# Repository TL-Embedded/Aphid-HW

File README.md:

# Aphid-HW

The Aphid Debugger provides a SWD and UART link via FT2232.

The 10 pin connector is compatible with the [10 pin standard here](https://github.com/TL-Embedded/SWD-UART-CTX-10).

The DTR signal can be used to apply +5V to the target `VCC AUX`.
The RTS signal can be used to ground the target `Detect`.

| Pin | Signal     | IO                  | Description |
| --- | ---------- | ------------------- | ----------- |
| 1   | VCC Target | Power input         | Reference voltage for logic IO |
| 2   | SWDIO      | Logic bidirectional | SWD Data line |
| 3   | GND        |                     | Common ground |
| 4   | SWCLK      | Logic output        | SWD Clock line |
| 5   | VCC Aux    | Power output        | 5V power output |
| 6   | N/C        |                     | Not connected |
| 7   | TX         | Logic output        | UART Transmit |
| 8   | Detect     | Open drain          | Debugger presence indicator |
| 9   | RX         | Logic input         | UART Receive |
| 10  | Reset      | Open drain          | Reset signal |

> [!CAUTION]
> DTR is usually automatically enabled by most terminal programs, which will enable `VCC Aux`. Ensure your target supports +5V on this pin, or remove R11 to disable this output.

# SWD interface

The SWD Debug interface is available on port 0 of the FT2232 as a D2XX device. It provides control of the SWD interface & Reset.

This is intended to be compatible with [OpenOCD](https://openocd.org/) using the [aphid-v1.cfg](./config/aphid-v1.cfg) config.

This may be copied into your openocd scripts folder, ie:
```
cp ./config/aphid-v1.cfg /usr/share/openocd/scripts/interface/ftdi/
```

The following example will validate the SWD interface is working (make sure to use the correct target).
```
openocd -f config/aphid-v1.cfg -f target/stm32g0x.cfg \
    -c "init" \
    -c "reset halt" \
    -c "mdw 0x08000000 4" \
    -c "resume" \
    -c "shutdown" \
```

# UART interface

The UART interface is available on port 1 of the FT2232 as a VCOM device.

The RTS and DTR signals are used for additional control:
 * RTS active enables the Detect signal
 * DTR active enables the VCC Aux output

# FTDI Programming

The FT2232 is programmed using [FTDI PROG](https://ftdichip.com/utilities/) via USB. The programming template is provided [here](./config/aphid.ftdiconf.xml).

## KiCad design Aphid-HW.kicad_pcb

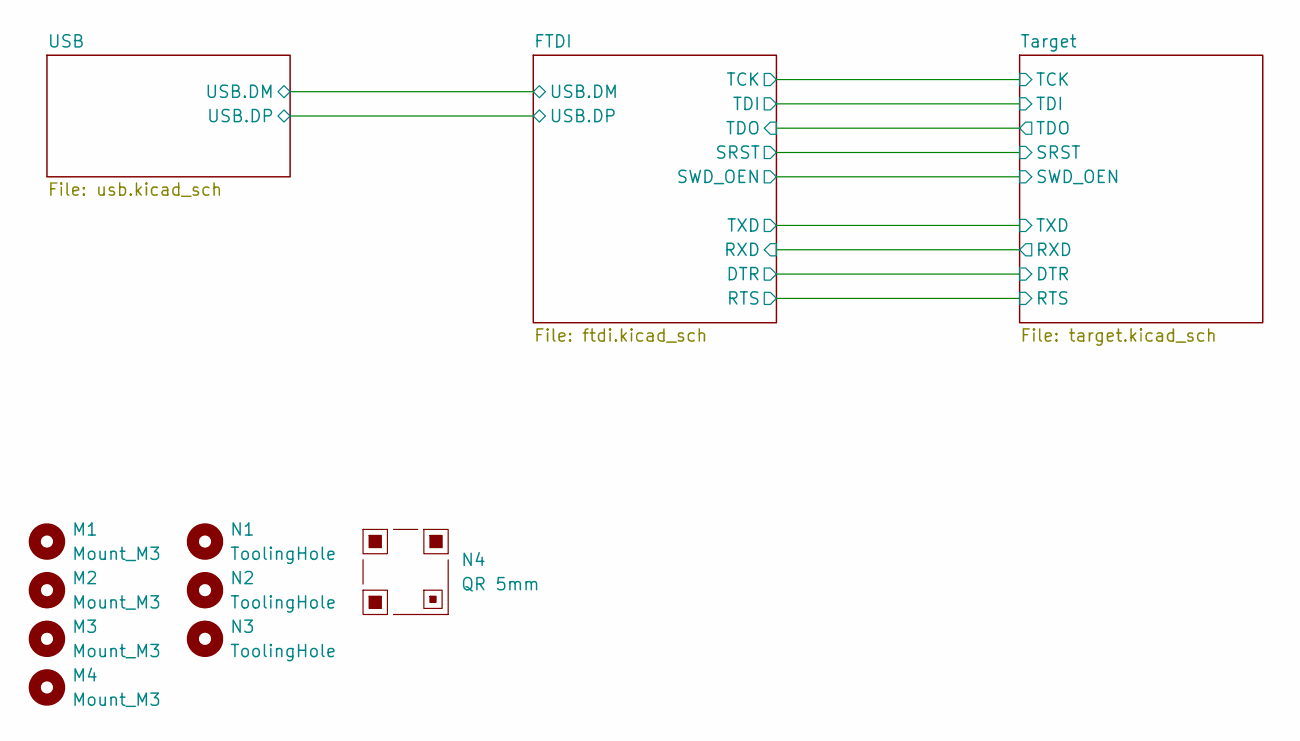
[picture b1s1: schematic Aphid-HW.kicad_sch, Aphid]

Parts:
M1, M2, M3, M4: Mount_M3
N1, N2, N3: ToolingHole; ToolingHole_1mm
N4: QR 5mm; QR_5mm_JLC

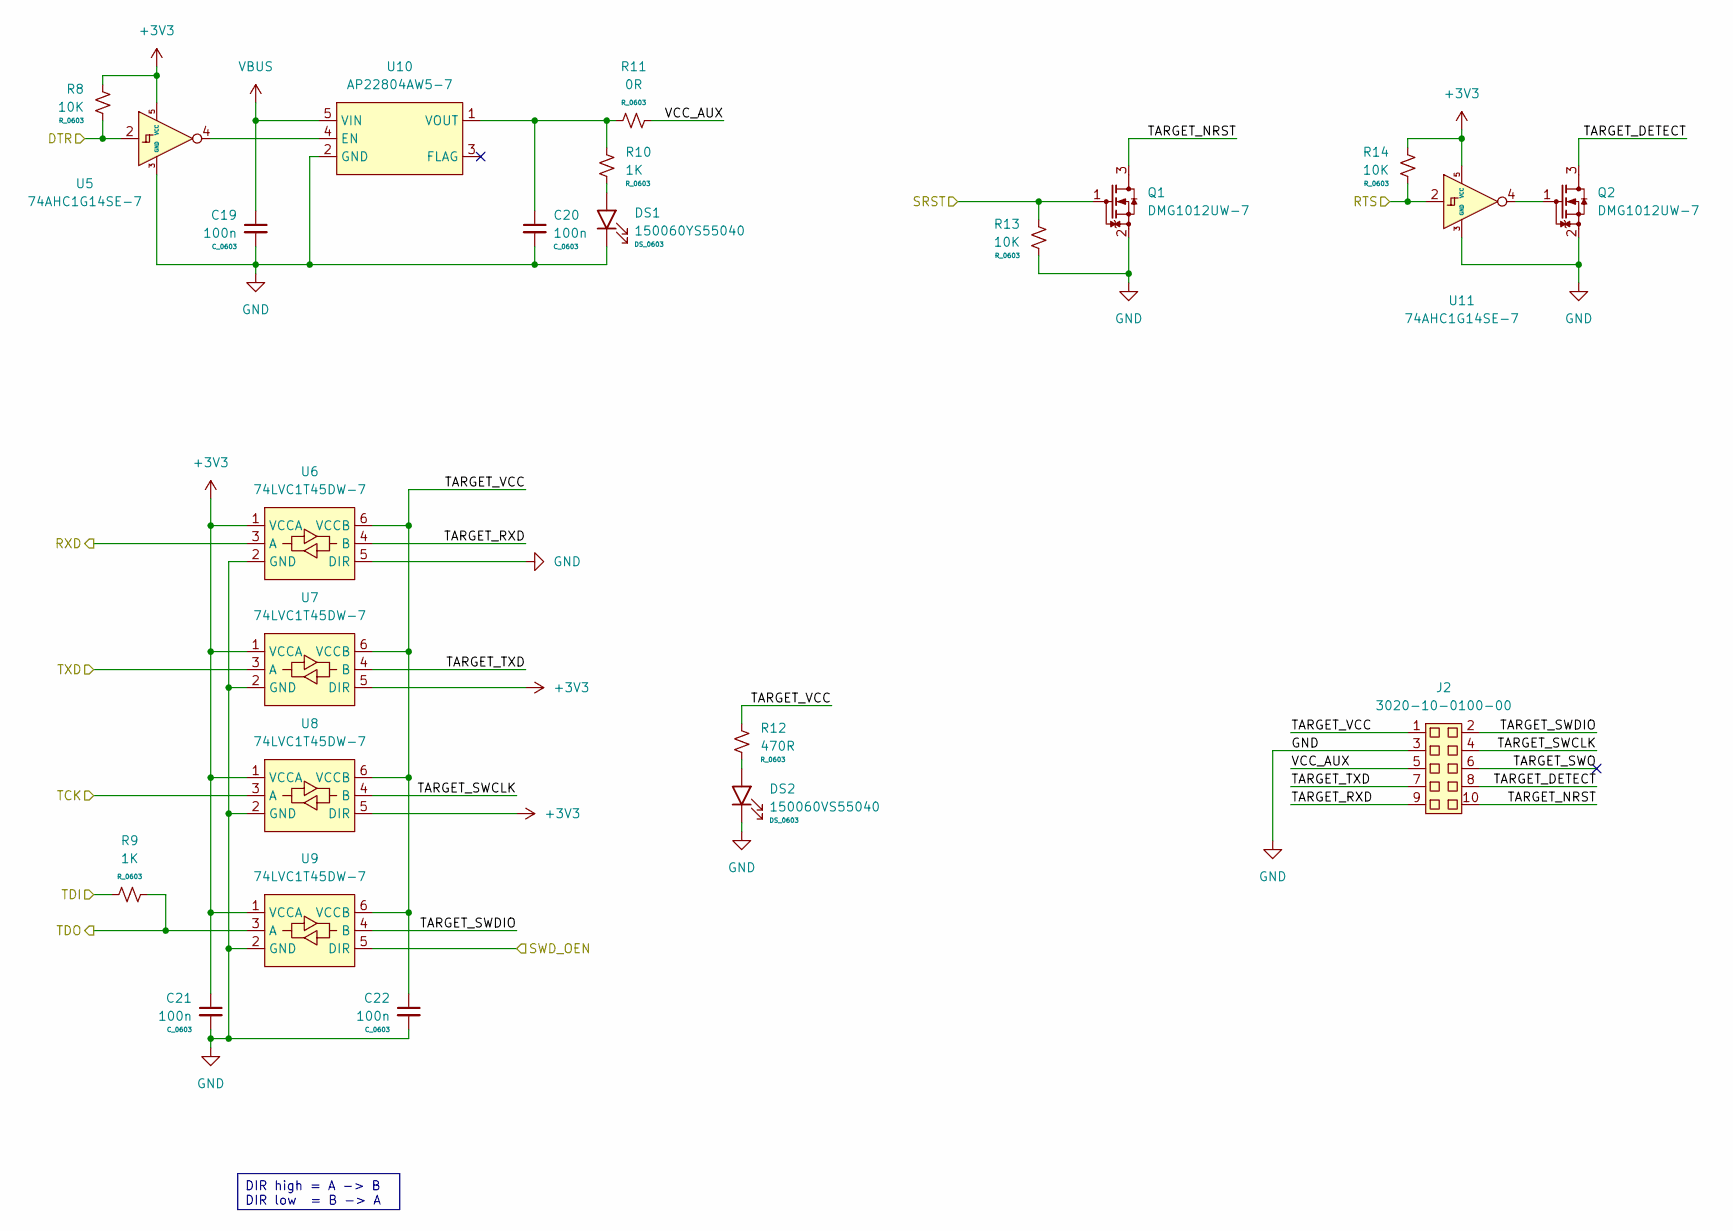
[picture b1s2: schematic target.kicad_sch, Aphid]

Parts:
C19, C20, C21, C22: 100n; C_0603
DS1: 150060YS55040; DS_0603
DS2: 150060VS55040; DS_0603
J2: 3020-10-0100-00; IDC-Header-02x10-2.54mm-Vert
Q1, Q2: DMG1012UW-7; SC70-3
R8, R13, R14: 10K; R_0603
R9, R10: 1K; R_0603
R11: 0R; R_0603
R12: 470R; R_0603
U5, U11: 74AHC1G14SE-7; SC70-5
U6, U7, U8, U9: 74LVC1T45DW-7; SC70-6
U10: AP22804AW5-7; SOT23_5

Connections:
+3V3: C21.1, R8.1, R14.1, U5.5 (VCC), U6.1 (VCCA), U7.1 (VCCA), U7.5 (DIR), U8.1 (VCCA), U8.5 (DIR), U9.1 (VCCA), U11.5 (VCC); also elsewhere on the board
/FTDI/DTR: R8.2, U5.2; also elsewhere on the board
/FTDI/RTS: R14.2, U11.2; also elsewhere on the board
/FTDI/RXD: U6.3 (A); also elsewhere on the board
/FTDI/SRST: Q1.1 (G), R13.1; also elsewhere on the board
/FTDI/SWD_OEN: U9.5 (DIR); also elsewhere on the board
/FTDI/TCK: U8.3 (A); also elsewhere on the board
/FTDI/TDI: R9.1; also elsewhere on the board
/FTDI/TDO: R9.2, U9.3 (A); also elsewhere on the board
/FTDI/TXD: U7.3 (A); also elsewhere on the board
/Target/TARGET_DETECT: J2.8, Q2.3 (D)
/Target/TARGET_NRST: J2.10, Q1.3 (D)
/Target/TARGET_RXD: J2.9, U6.4 (B)
/Target/TARGET_SWCLK: J2.4, U8.4 (B)
/Target/TARGET_SWDIO: J2.2, U9.4 (B)
/Target/TARGET_SWO: J2.6
/Target/TARGET_TXD: J2.7, U7.4 (B)
/Target/TARGET_VCC: C22.1, J2.1, R12.1, U6.6 (VCCB), U7.6 (VCCB), U8.6 (VCCB), U9.6 (VCCB)
/Target/VCC_AUX: J2.5, R11.2
GND: C19.2, C20.2, C21.2, C22.2, DS1.1 (K), DS2.1 (K), J2.3, Q1.2 (S), Q2.2 (S), R13.2, U5.3 (GND), U6.2 (GND), U6.5 (DIR), U7.2 (GND), U8.2 (GND), U9.2 (GND), U10.2 (GND), U11.3 (GND); also elsewhere on the board
unnamed: DS1.2 (A), R10.2
unnamed: DS2.2 (A), R12.2
unnamed: Q2.1 (G), U11.4
unnamed: U5.4, U10.4 (EN)
unnamed: C20.1, R10.1, R11.1, U10.1 (VOUT)
VBUS: C19.1, U10.5 (VIN); also elsewhere on the board

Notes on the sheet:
DIR high = A -> B DIR low = B -> A

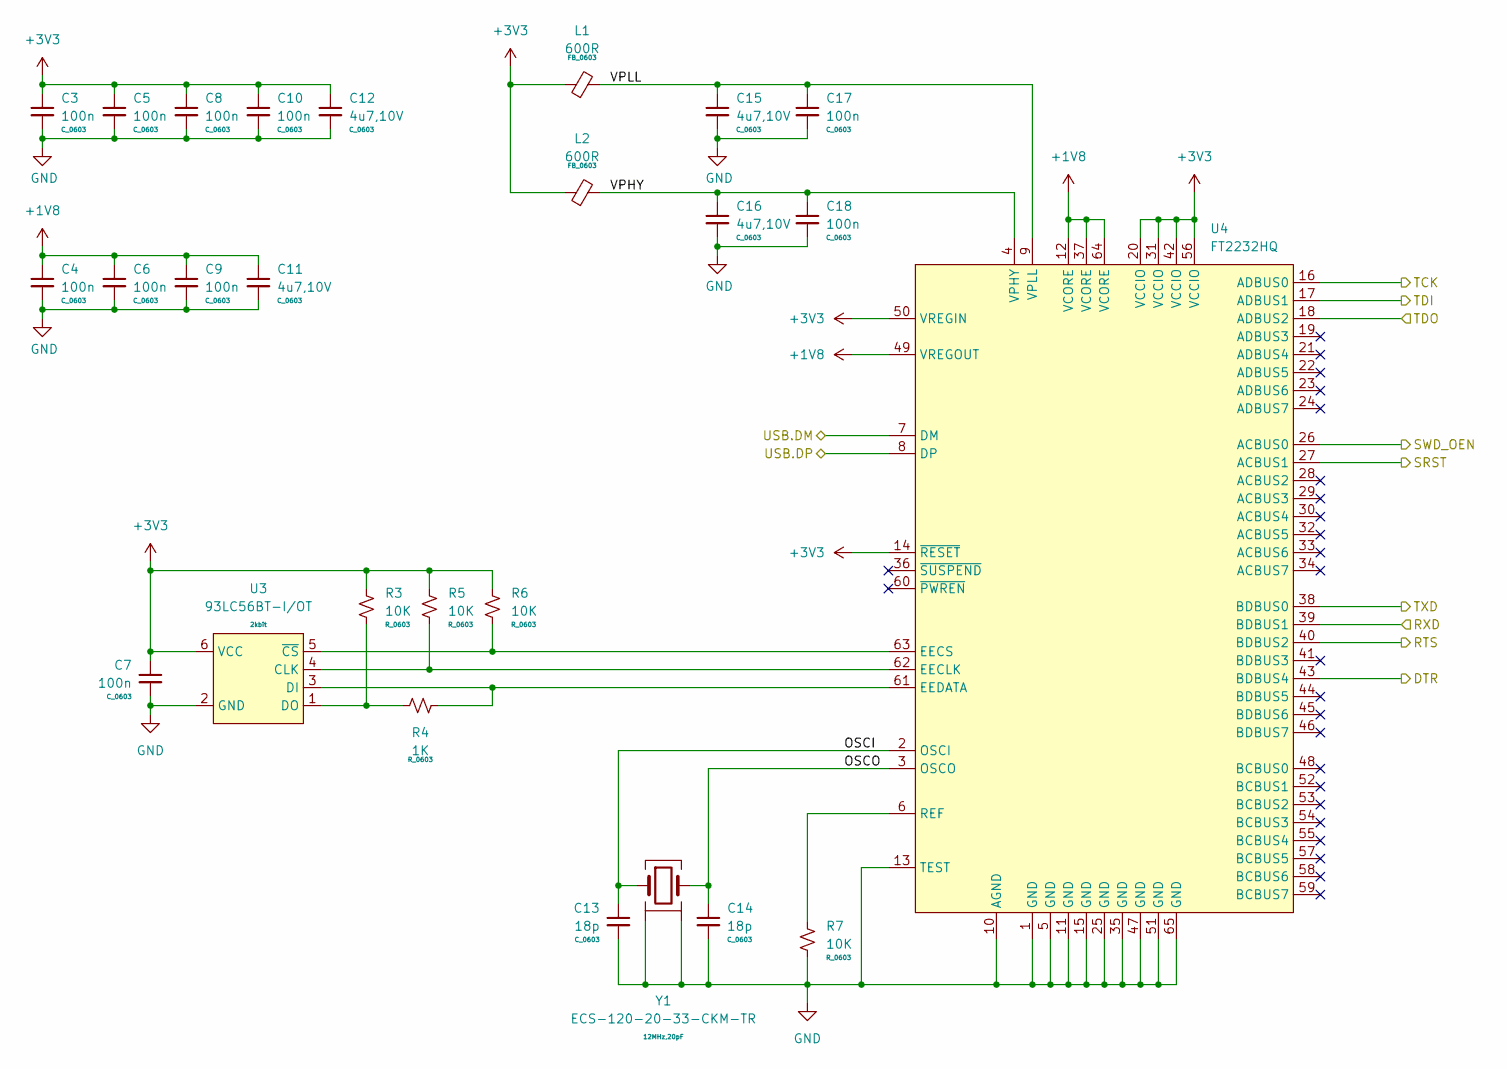
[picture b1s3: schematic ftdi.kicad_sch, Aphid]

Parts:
C3, C4, C5, C6, C7, C8, C9, C10, C17, C18: 100n; C_0603
C11, C12, C15, C16: 4u7,10V; C_0603
C13, C14: 18p; C_0603
L1, L2: 600R; FB_0603
R3, R5, R6, R7: 10K; R_0603
R4: 1K; R_0603
U3: 93LC56BT-I/OT; SOT23_6
U4: FT2232HQ; QFN64_05_9x9_EP_FTDI
Y1: ECS-120-20-33-CKM-TR; Crystal_SMD4_3.2x2.5

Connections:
+1V8: C4.1, C6.1, C9.1, C11.1, U4.12 (VCORE), U4.37 (VCORE), U4.49 (VREGOUT), U4.64 (VCORE)
+3V3: C3.1, C5.1, C7.1, C8.1, C10.1, C12.1, L1.1, L2.1, R3.1, R5.1, R6.1, U3.6 (VCC), U4.14 (~RESET), U4.20 (VCCIO), U4.31 (VCCIO), U4.42 (VCCIO), U4.50 (VREGIN), U4.56 (VCCIO); also elsewhere on the board
/FTDI/DTR: U4.43 (BDBUS4); also elsewhere on the board
/FTDI/OSCI: C13.1, U4.2 (OSCI), Y1.1
/FTDI/OSCO: C14.1, U4.3 (OSCO), Y1.3
/FTDI/RTS: U4.40 (BDBUS2); also elsewhere on the board
/FTDI/RXD: U4.39 (BDBUS1); also elsewhere on the board
/FTDI/SRST: U4.27 (ACBUS1); also elsewhere on the board
/FTDI/SWD_OEN: U4.26 (ACBUS0); also elsewhere on the board
/FTDI/TCK: U4.16 (ADBUS0); also elsewhere on the board
/FTDI/TDI: U4.17 (ADBUS1); also elsewhere on the board
/FTDI/TDO: U4.18 (ADBUS2); also elsewhere on the board
/FTDI/TXD: U4.38 (BDBUS0); also elsewhere on the board
/FTDI/USB.DM: U4.7 (DM); also elsewhere on the board
/FTDI/USB.DP: U4.8 (DP); also elsewhere on the board
/FTDI/VPHY: C16.1, C18.1, L2.2, U4.4 (VPHY)
/FTDI/VPLL: C15.1, C17.1, L1.2, U4.9 (VPLL)
GND: C3.2, C4.2, C5.2, C6.2, C7.2, C8.2, C9.2, C10.2, C11.2, C12.2, C13.2, C14.2, C15.2, C16.2, C17.2, C18.2, R7.2, U3.2 (GND), U4.1 (GND), U4.5 (GND), U4.10 (AGND), U4.11 (GND), U4.13 (TEST), U4.15 (GND), U4.25 (GND), U4.35 (GND), U4.47 (GND), U4.51 (GND), U4.65 (GND), Y1.2, Y1.4; also elsewhere on the board
unnamed: R5.2, U3.4 (CLK), U4.62 (EECLK)
unnamed: R4.1, U3.3 (DI), U4.61 (EEDATA)
unnamed: R3.2, R4.2, U3.1 (DO)
unnamed: R6.2, U3.5 (~CS), U4.63 (EECS)
unnamed: R7.1, U4.6 (REF)

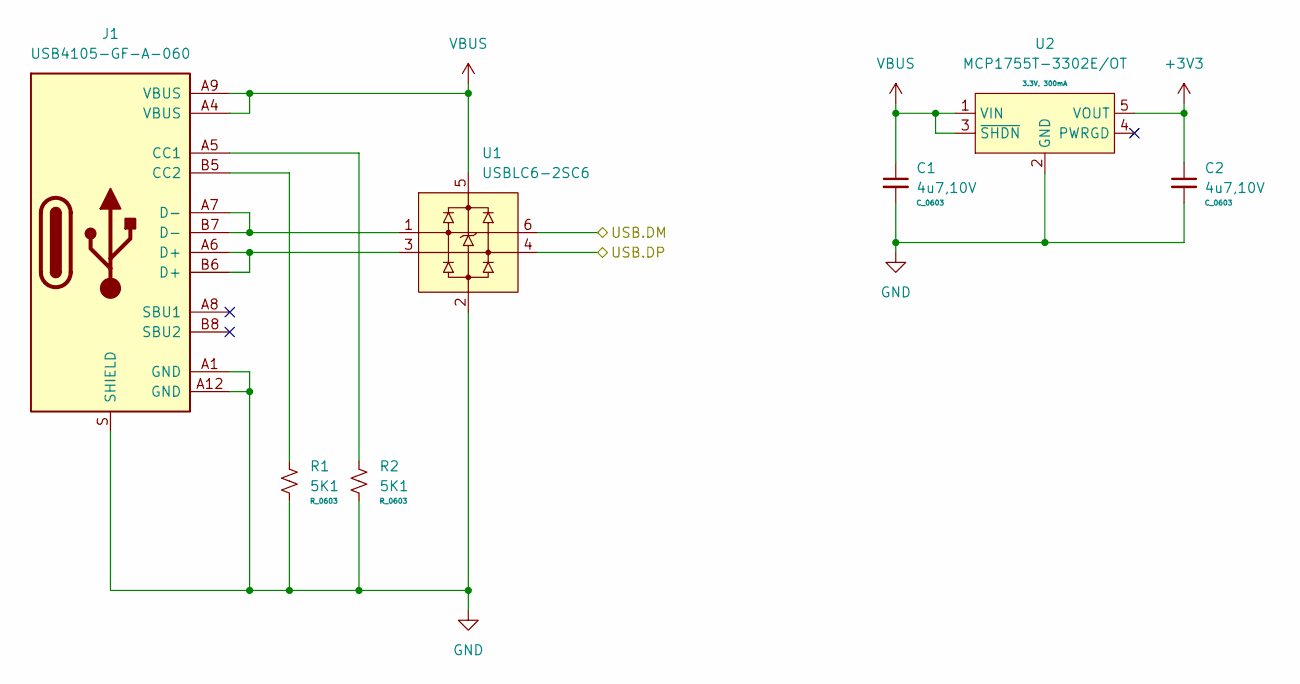
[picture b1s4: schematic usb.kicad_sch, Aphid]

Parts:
C1, C2: 4u7,10V; C_0603
J1: USB4105-GF-A-060; USB_C_USB4105-GF-A-060
R1, R2: 5K1; R_0603
U1: USBLC6-2SC6; SOT23_6
U2: MCP1755T-3302E/OT; SOT23_5

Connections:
+3V3: C2.1, U2.5 (VOUT); also elsewhere on the board
/FTDI/USB.DM: U1.6; also elsewhere on the board
/FTDI/USB.DP: U1.4; also elsewhere on the board
GND: C1.2, C2.2, J1.A1 (GND), J1.A12 (GND), J1.S (SHIELD), R1.2, R2.2, U1.2, U2.2 (GND); also elsewhere on the board
unnamed: J1.A5 (CC1), R2.1
unnamed: J1.B5 (CC2), R1.1
unnamed: J1.A6 (D+), J1.B6 (D+), U1.3
unnamed: J1.A7 (D-), J1.B7 (D-), U1.1
VBUS: C1.1, J1.A4 (VBUS), J1.A9 (VBUS), U1.5, U2.1 (VIN), U2.3 (~SHDN); also elsewhere on the board

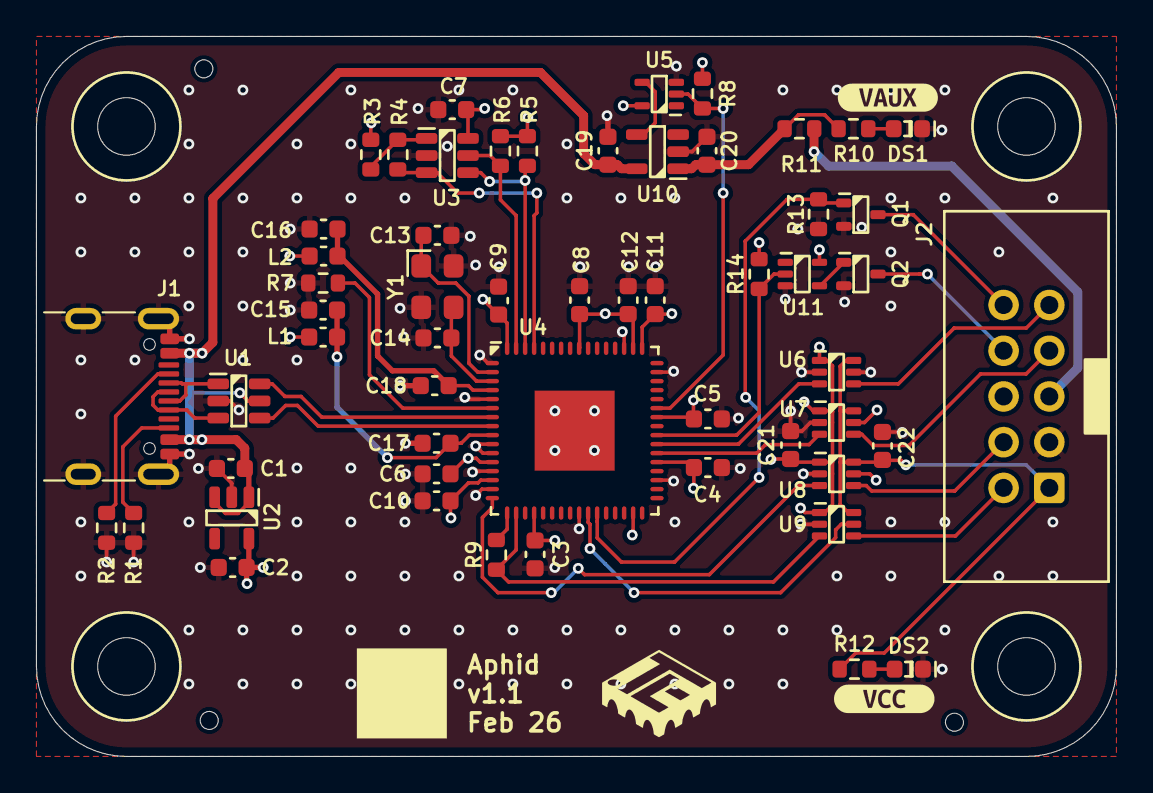
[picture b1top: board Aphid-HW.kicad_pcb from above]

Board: 4 copper layers, 60.0 x 40.0 mm, 66 parts (0 on the bottom side), 41 nets.

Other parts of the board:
kibuzzard-69A2682E: G***; kibuzzard-69A2682E
kibuzzard-69A26839: G***; kibuzzard-69A26839

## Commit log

2026-02-28 Update output settings
2026-02-28 Add a readme
2026-03-21 Rework logic gates
    Rename to aphid
2026-03-23 Update PCB layout
2026-03-23 Update output scripts
2026-03-23 Update output colours.
2026-04-26 Add openOCD conf
    Update readme
2026-04-26 Remove orphaned x-link file
